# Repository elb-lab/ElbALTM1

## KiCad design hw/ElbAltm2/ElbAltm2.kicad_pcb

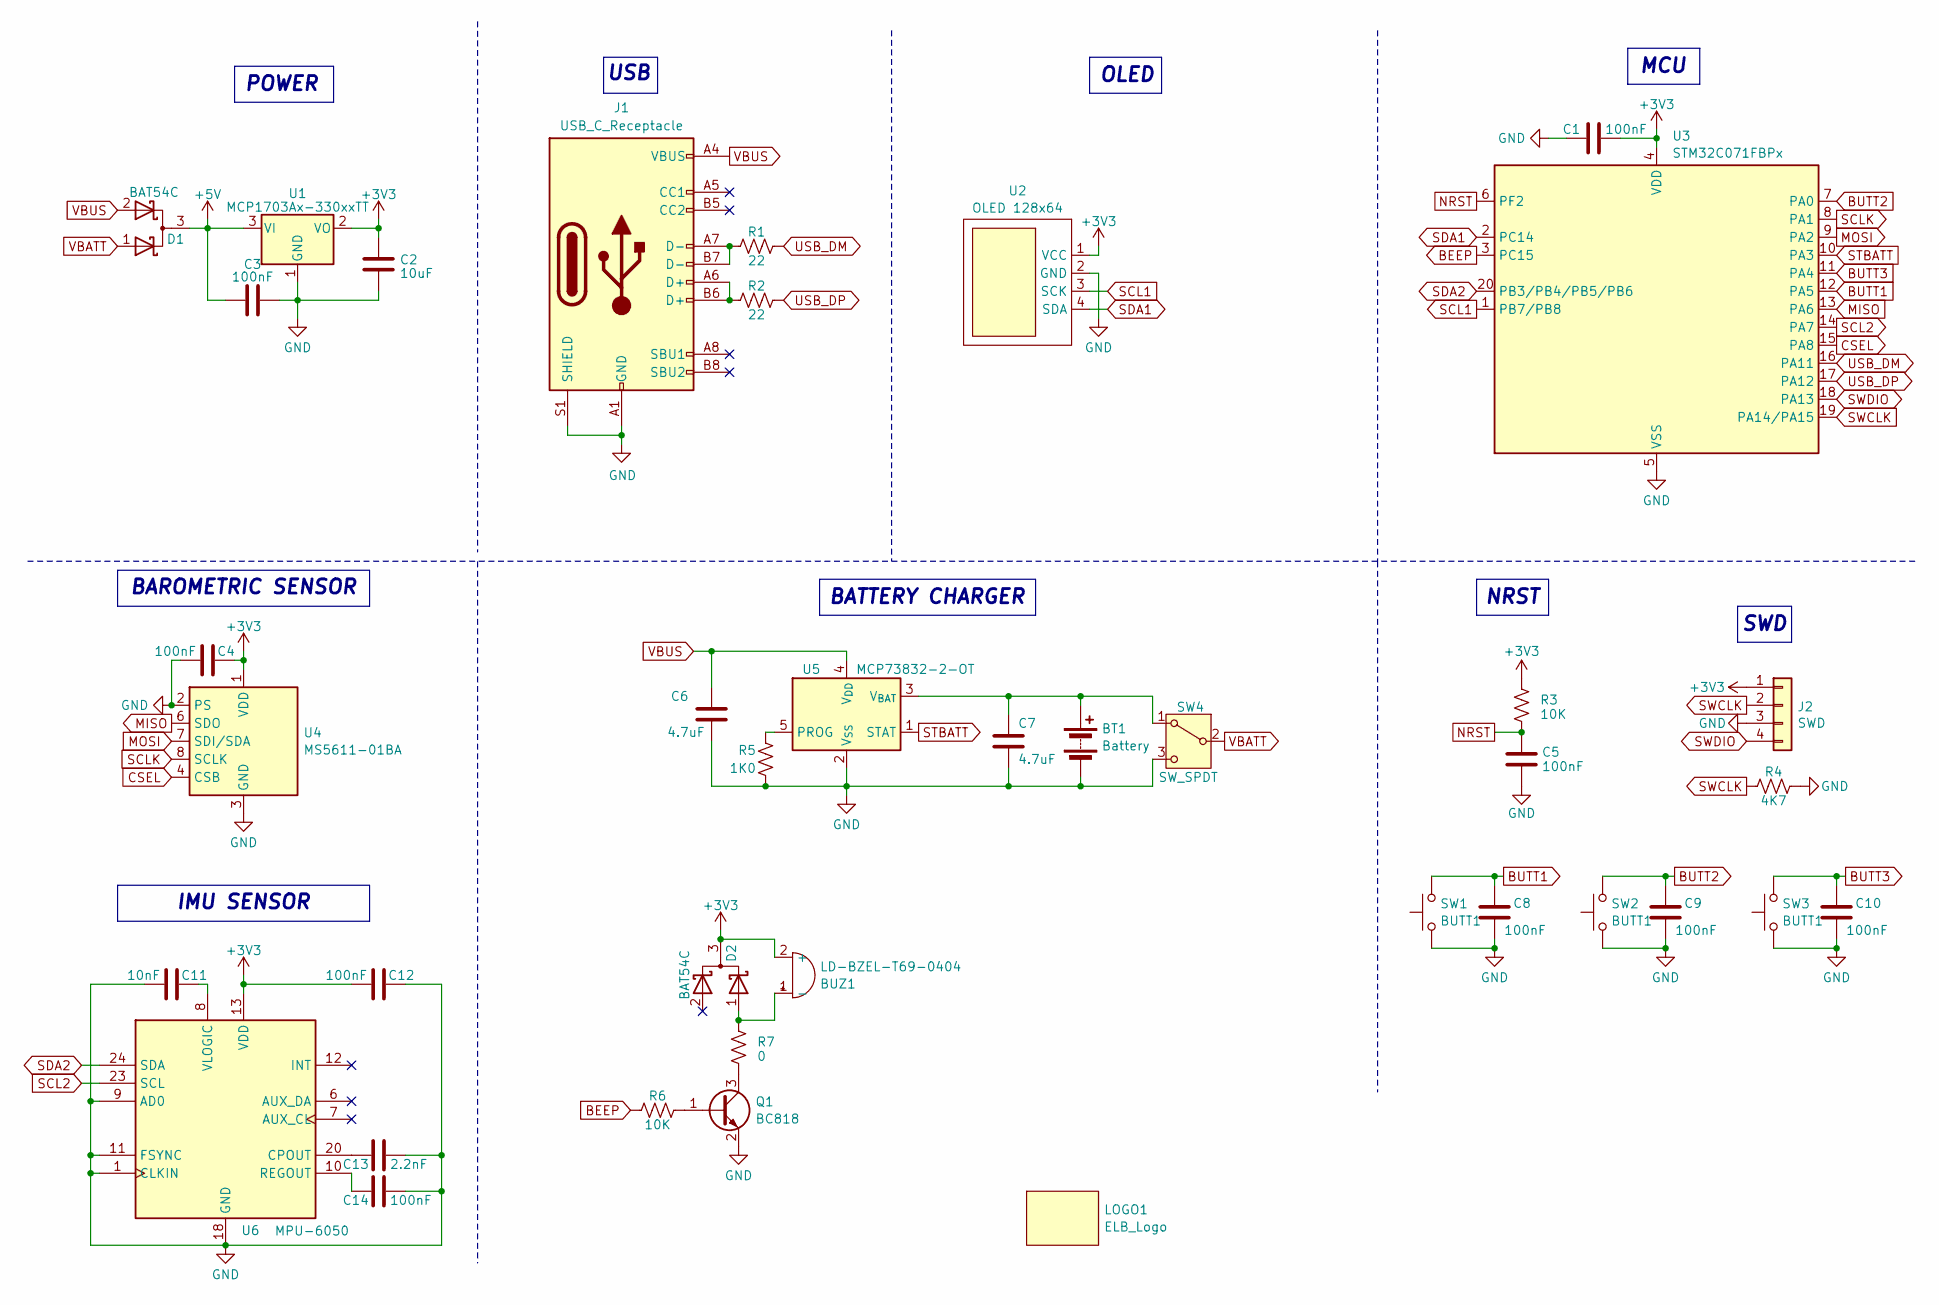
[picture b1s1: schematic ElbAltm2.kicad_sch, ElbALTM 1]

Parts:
BT1: Battery; JST_PH_S2B-PH-K_1x02_P2.00mm_Horizontal
BUZ1: LD-BZEL-T69-0404
C1, C3, C4, C5, C8, C9, C10, C12, C14: 100nF; C_0805_2012Metric_Pad1.18x1.45mm_HandSolder
C2: 10uF; C_0805_2012Metric_Pad1.18x1.45mm_HandSolder
C6, C7: 4.7uF; C_0805_2012Metric_Pad1.18x1.45mm_HandSolder
C11: 10nF; C_0805_2012Metric_Pad1.18x1.45mm_HandSolder
C13: 2.2nF; C_0805_2012Metric_Pad1.18x1.45mm_HandSolder
D1, D2: BAT54C; SOT-23
J1: USB_C_Receptacle; USB_C_Receptacle_HRO_TYPE-C-31-M-12
J2: SWD; PinHeader_1x04_P2.54mm_Horizontal
LOGO1: ELB_Logo; HDO_very_small_bn
Q1: BC818; SOT-23
R1, R2: 22; R_0805_2012Metric_Pad1.20x1.40mm_HandSolder
R3, R6: 10K; R_0805_2012Metric_Pad1.20x1.40mm_HandSolder
R4: 4K7; R_0805_2012Metric_Pad1.20x1.40mm_HandSolder
R5: 1K0; R_0805_2012Metric_Pad1.20x1.40mm_HandSolder
R7: 0; R_0805_2012Metric_Pad1.20x1.40mm_HandSolder
SW1, SW2, SW3: BUTT1; SW_Push_1P1T_NO_E-Switch_TL3301NxxxxxG
SW4: SW_SPDT; SW_SPDT_CK_JS102011SAQN
U1: MCP1703Ax-330xxTT; SOT-23
U2: OLED 128x64; oled128x64_wo_holes
U3: STM32C071FBPx; TSSOP-20_4.4x6.5mm_P0.65mm
U4: MS5611-01BA; LGA-8_3x5mm_P1.25mm
U5: MCP73832-2-OT; SOT-23-5
U6: MPU-6050; InvenSense_QFN-24_4x4mm_P0.5mm

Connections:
+3V3: BUZ1.2 (+), C1.1, C2.1, C4.1, C12.2, D2.3 (K), J2.1, R3.1, U1.2 (VO), U2.1 (VCC), U3.4 (VDD), U4.1 (VDD), U6.13 (VDD)
+5V: C3.1, D1.3 (K), U1.3 (VI)
BEEP: R6.1, U3.3 (PC15)
BUTT1: C8.1, SW1.2, U3.12 (PA5)
BUTT2: C9.1, SW2.2, U3.7 (PA0)
BUTT3: C10.1, SW3.2, U3.11 (PA4)
CSEL: U3.15 (PA8), U4.4 (CSB), U4.5 (CSB)
GND: BT1.2 (-), C1.2, C2.2, C3.2, C4.2, C5.2, C6.2, C7.2, C8.2, C9.2, C10.2, C11.2, C12.1, C13.2, C14.2, J1.A1 (GND), J1.A12 (GND), J1.B1 (GND), J1.B12 (GND), J1.S1 (SHIELD), J2.3, Q1.2 (E), R4.2, R5.2, SW1.1, SW2.1, SW3.1, SW4.3 (C), U1.1 (GND), U2.2 (GND), U3.5 (VSS), U4.2 (PS), U4.3 (GND), U5.2 (V_{SS}), U6.1 (CLKIN), U6.9 (AD0), U6.11 (FSYNC), U6.18 (GND)
MISO: U3.13 (PA6), U4.6 (SDO)
MOSI: U3.9 (PA2), U4.7 (SDI/SDA)
NRST: C5.1, R3.2, U3.6 (PF2)
unnamed: BT1.1 (+), C7.1, SW4.1 (A), U5.3 (V_{BAT})
unnamed: BUZ1.1 (-), D2.1 (A), R7.1
unnamed: J1.A6 (D+), J1.B6 (D+), R2.1
unnamed: J1.A7 (D-), J1.B7 (D-), R1.1
unnamed: Q1.1 (B), R6.2
unnamed: Q1.3 (C), R7.2
unnamed: R5.1, U5.5 (PROG)
unnamed: C13.1, U6.20 (CPOUT)
unnamed: C14.1, U6.10 (REGOUT)
unnamed: C11.1, U6.8 (VLOGIC)
SCL1: U2.3 (SCK), U3.1 (PB7/PB8)
SCL2: U3.14 (PA7), U6.23 (SCL)
SCLK: U3.8 (PA1), U4.8 (SCLK)
SDA1: U2.4 (SDA), U3.2 (PC14)
SDA2: U3.20 (PB3/PB4/PB5/PB6), U6.24 (SDA)
STBATT: U3.10 (PA3), U5.1 (STAT)
SWCLK: J2.2, R4.1, U3.19 (PA14/PA15)
SWDIO: J2.4, U3.18 (PA13)
USB_DM: R1.2, U3.16 (PA11)
USB_DP: R2.2, U3.17 (PA12)
VBATT: D1.1 (A), SW4.2 (B)
VBUS: C6.1, D1.2 (A), J1.A4 (VBUS), J1.A9 (VBUS), J1.B4 (VBUS), J1.B9 (VBUS), U5.4 (V_{DD})

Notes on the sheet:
SWD
IMU SENSOR
POWER
NRST
USB
BATTERY CHARGER
BAROMETRIC SENSOR
OLED
MCU

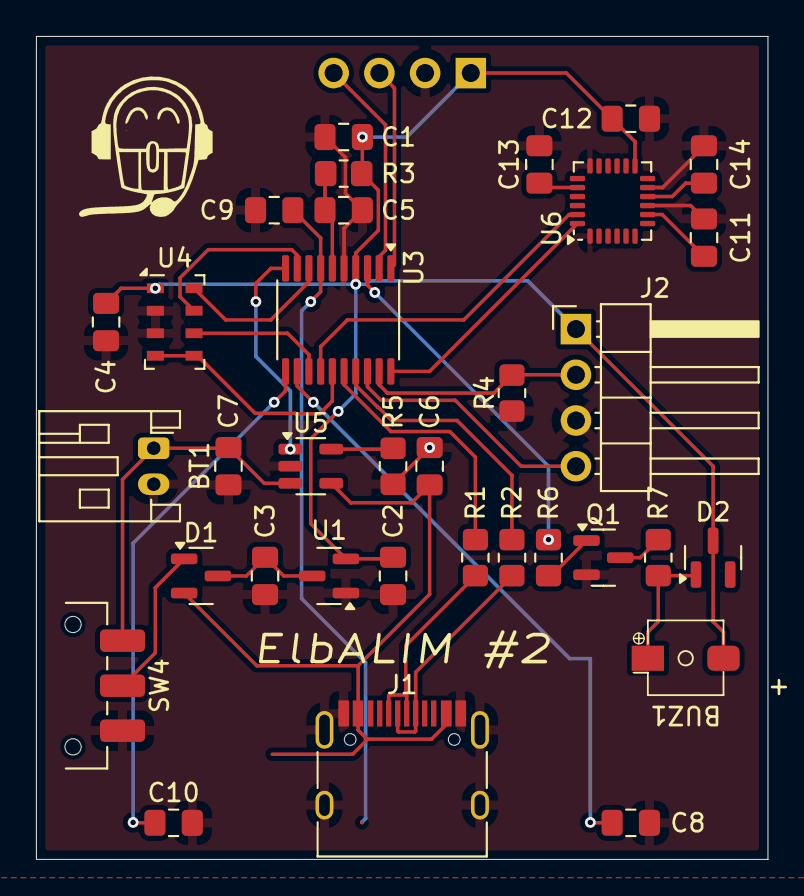
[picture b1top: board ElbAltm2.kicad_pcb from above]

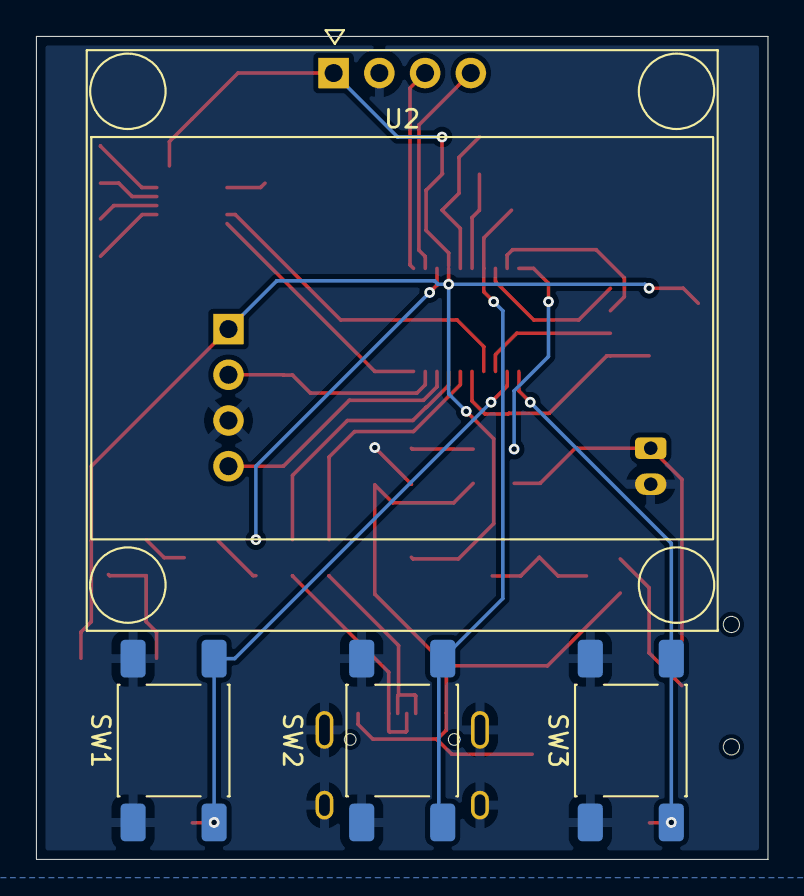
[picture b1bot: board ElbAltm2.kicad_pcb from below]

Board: 2 copper layers, 40.6 x 45.7 mm, 39 parts (4 on the bottom side), 33 nets.

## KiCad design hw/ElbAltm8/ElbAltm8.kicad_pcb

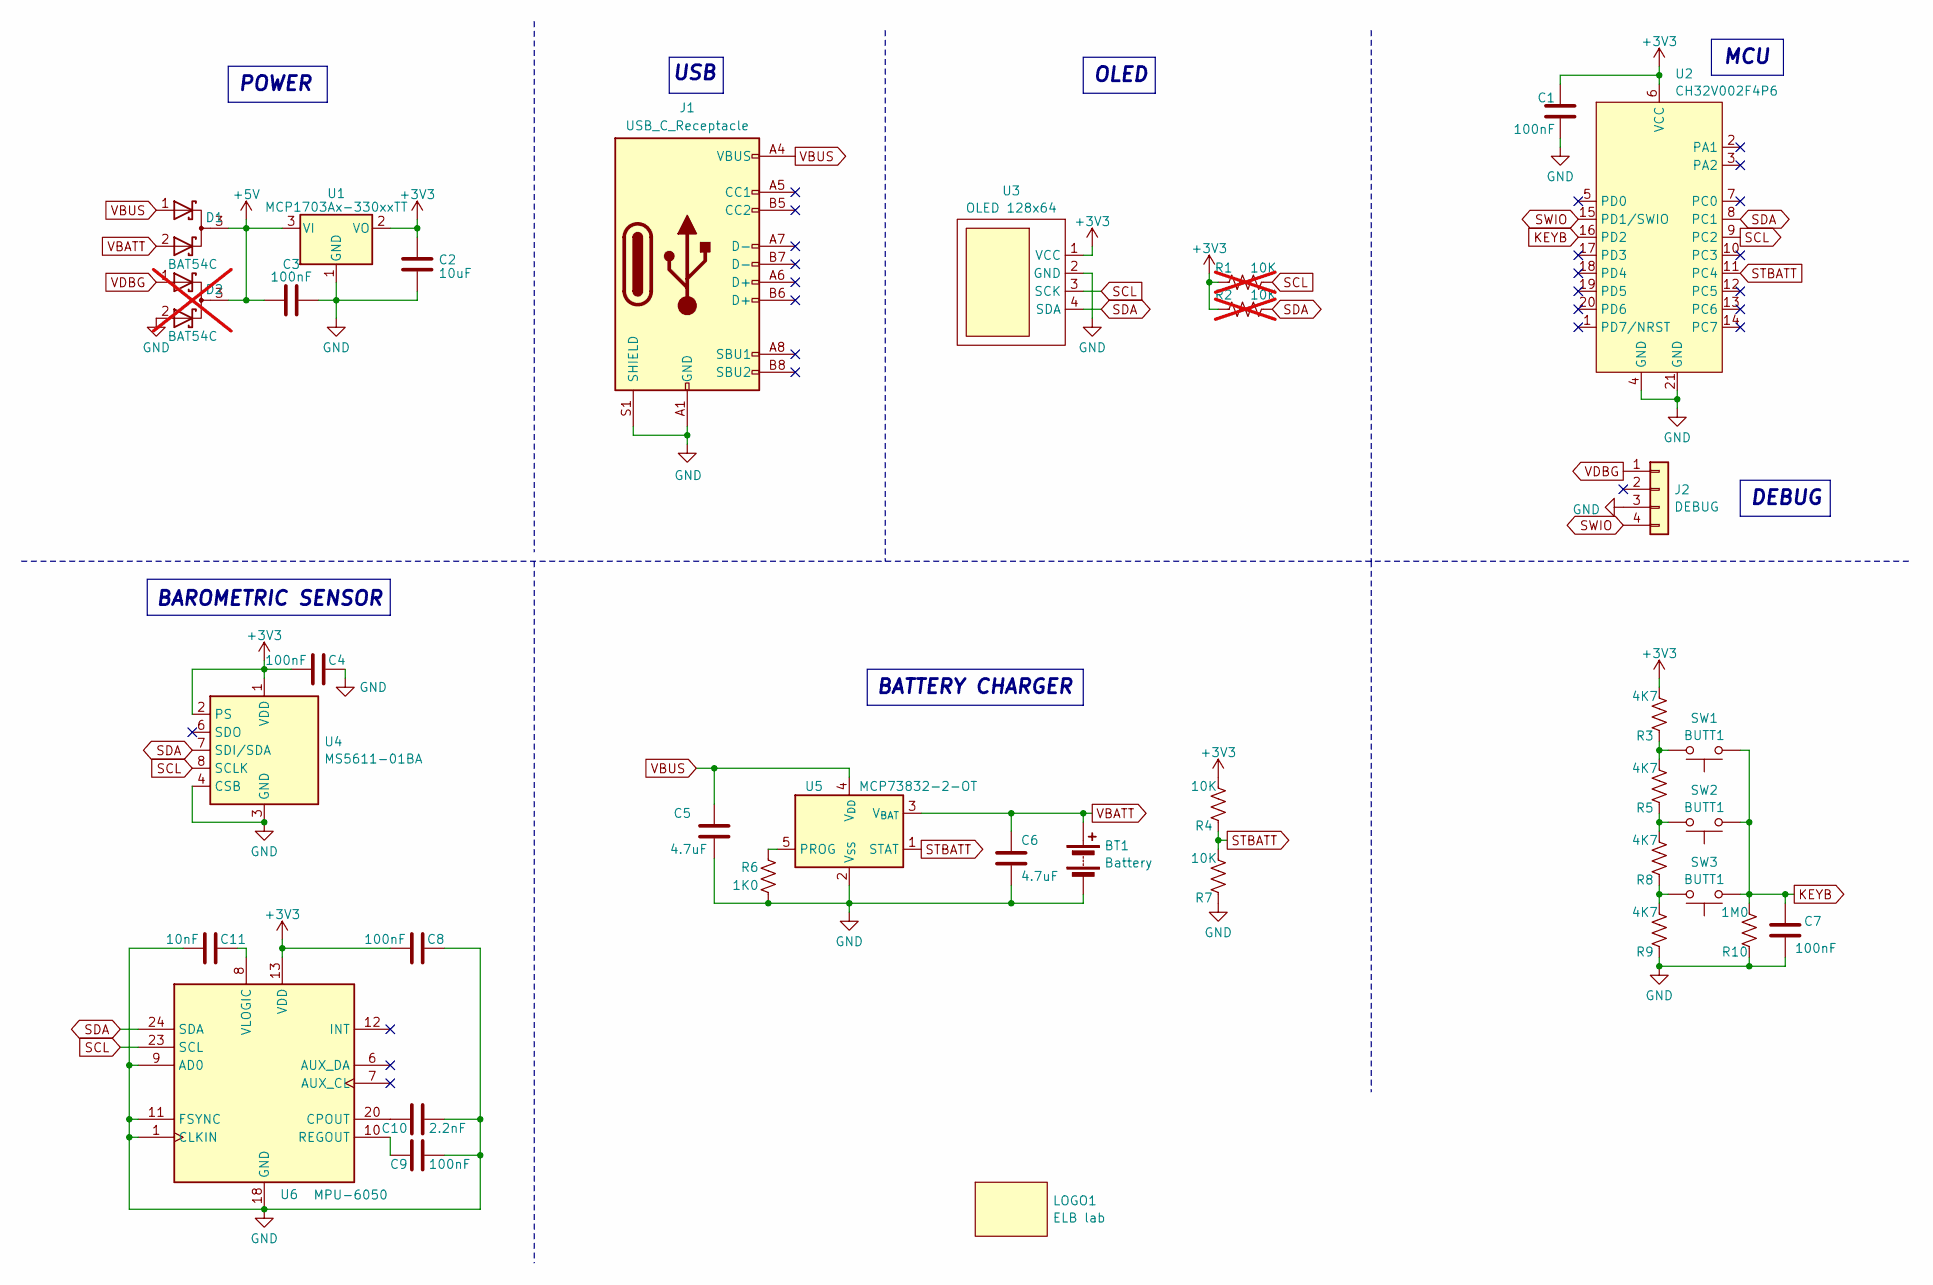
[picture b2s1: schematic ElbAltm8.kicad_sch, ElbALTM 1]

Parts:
BT1: Battery; JST_PH_B2B-PH-K_1x02_P2.00mm_Vertical
C1, C3, C4, C7, C8, C9: 100nF; C_0805_2012Metric_Pad1.18x1.45mm_HandSolder
C2: 10uF; C_0805_2012Metric_Pad1.18x1.45mm_HandSolder
C5, C6: 4.7uF; C_0805_2012Metric_Pad1.18x1.45mm_HandSolder
C10: 2.2nF; C_0805_2012Metric_Pad1.18x1.45mm_HandSolder
C11: 10nF; C_0805_2012Metric_Pad1.18x1.45mm_HandSolder
D1: BAT54C; SOT-23
D2: BAT54C; SOT-23; not fitted
J1: USB_C_Receptacle; USB_C_Receptacle_HRO_TYPE-C-31-M-12
J2: DEBUG; PinHeader_1x04_P2.54mm_Horizontal
LOGO1: ELB lab; HDO_very_small_bn
R1, R2: 10K; R_0805_2012Metric_Pad1.20x1.40mm_HandSolder; not fitted
R3, R5, R8, R9: 4K7; R_0805_2012Metric_Pad1.20x1.40mm_HandSolder
R4, R7: 10K; R_0805_2012Metric_Pad1.20x1.40mm_HandSolder
R6: 1K0; R_0805_2012Metric_Pad1.20x1.40mm_HandSolder
R10: 1M0; R_0805_2012Metric_Pad1.20x1.40mm_HandSolder
SW1, SW2, SW3: BUTT1; SW_PUSH_6mm_H5mm
U1: MCP1703Ax-330xxTT; SOT-23
U2: CH32V002F4P6; QFN-20-1EP_3x3mm_P0.4mm_EP1.65x1.65mm_ThermalVias
U3: OLED 128x64; oled128x64_wo_holes
U4: MS5611-01BA; LGA-8_3x5mm_P1.25mm
U5: MCP73832-2-OT; SOT-23-5
U6: MPU-6050; InvenSense_QFN-24_4x4mm_P0.5mm

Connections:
+3V3: C1.1, C2.1, C4.2, C8.2, R1.1, R2.1, R3.2, R4.2, U1.2 (VO), U2.6 (VCC), U3.1 (VCC), U4.1 (VDD), U4.2 (PS), U6.13 (VDD)
+5V: C3.1, D1.3 (K), D2.3 (K), U1.3 (VI)
GND: BT1.2 (-), C1.2, C2.2, C3.2, C4.1, C5.2, C6.2, C7.2, C8.1, C9.2, C10.2, C11.2, D2.2 (A), J1.A1 (GND), J1.A12 (GND), J1.B1 (GND), J1.B12 (GND), J1.S1 (SHIELD), J2.3, R6.2, R7.1, R9.1, R10.1, U1.1 (GND), U2.4 (GND), U2.21 (GND), U3.2 (GND), U4.3 (GND), U4.4 (CSB), U4.5 (CSB), U5.2 (V_{SS}), U6.1 (CLKIN), U6.9 (AD0), U6.11 (FSYNC), U6.18 (GND)
KEYB: C7.1, R10.2, SW1.1, SW2.1, SW3.1, U2.16 (PD2)
unnamed: R3.1, R5.2, SW1.2
unnamed: R5.1, R8.2, SW2.2
unnamed: R8.1, R9.2, SW3.2
unnamed: R6.1, U5.5 (PROG)
unnamed: C10.1, U6.20 (CPOUT)
unnamed: C9.1, U6.10 (REGOUT)
unnamed: C11.1, U6.8 (VLOGIC)
SCL: R1.2, U2.9 (PC2), U3.3 (SCK), U4.8 (SCLK), U6.23 (SCL)
SDA: R2.2, U2.8 (PC1), U3.4 (SDA), U4.7 (SDI/SDA), U6.24 (SDA)
STBATT: R4.1, R7.2, U2.11 (PC4), U5.1 (STAT)
SWIO: J2.4, U2.15 (PD1/SWIO)
VBATT: BT1.1 (+), C6.1, D1.2 (A), U5.3 (V_{BAT})
VBUS: C5.1, D1.1 (A), J1.A4 (VBUS), J1.A9 (VBUS), J1.B4 (VBUS), J1.B9 (VBUS), U5.4 (V_{DD})
VDBG: D2.1 (A), J2.1

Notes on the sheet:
POWER
USB
BATTERY CHARGER
DEBUG
BAROMETRIC SENSOR
OLED
MCU

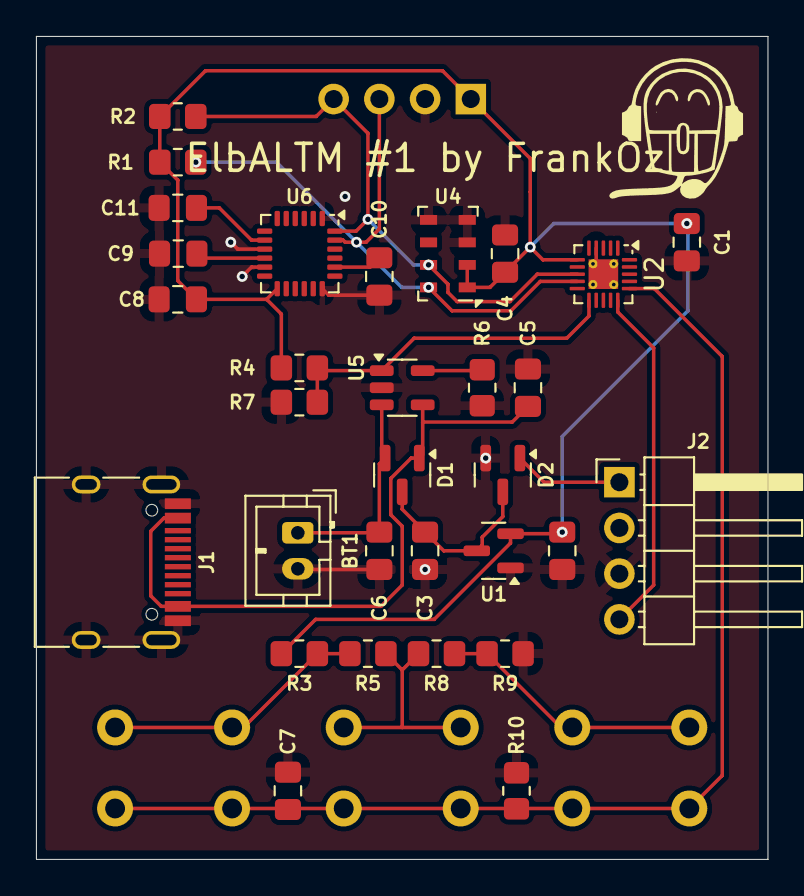
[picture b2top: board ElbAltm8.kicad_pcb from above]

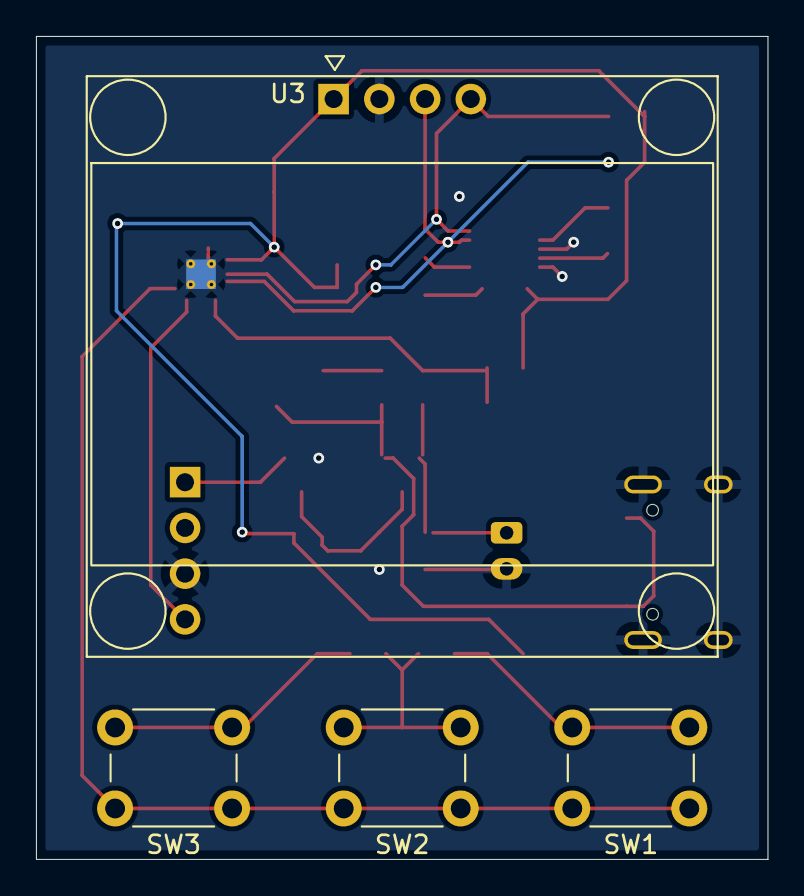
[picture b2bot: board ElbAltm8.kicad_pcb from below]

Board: 2 copper layers, 40.6 x 45.7 mm, 36 parts (4 on the bottom side), 18 nets.

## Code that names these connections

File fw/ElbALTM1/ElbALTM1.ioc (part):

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Mcu.Name=STM32C071FBPx
Mcu.Package=TSSOP20_GP
Mcu.UserName=STM32C071FBPx
PA0.GPIOParameters=GPIO_PuPd,GPIO_Label,GPIO_ModeDefaultEXTI
PA0.GPIO_Label=BUTT2
PA0.GPIO_ModeDefaultEXTI=GPIO_MODE_IT_FALLING
PA0.GPIO_PuPd=GPIO_PULLUP
PA0.Signal=GPXTI0
PA1.GPIOParameters=GPIO_Speed,GPIO_Label
PA1.GPIO_Label=SCLK
PA1.GPIO_Speed=GPIO_SPEED_FREQ_VERY_HIGH
PA1.Mode=Full_Duplex_Master
PA1.Signal=SPI1_SCK
PA11\ [PA9].Signal=USB_DM
PA12\ [PA10].Signal=USB_DP
PA13.GPIOParameters=GPIO_Label
PA13.GPIO_Label=SWDIO
PA13.Mode=Serial_Wire
PA13.Signal=DEBUG_SWDIO
PA14-BOOT0.GPIOParameters=GPIO_Label
PA14-BOOT0.GPIO_Label=SWCLK
PA14-BOOT0.Mode=Serial_Wire
PA14-BOOT0.Signal=DEBUG_SWCLK
PA14-BOOT0__PA15.StandardMode=true
PA2.GPIOParameters=GPIO_Speed,GPIO_Label
PA2.GPIO_Label=MOSI
PA2.GPIO_Speed=GPIO_SPEED_FREQ_VERY_HIGH
PA2.Mode=Full_Duplex_Master
PA2.Signal=SPI1_MOSI
PA3.GPIOParameters=GPIO_PuPd,GPIO_Label
PA3.GPIO_Label=STBATT
PA3.GPIO_PuPd=GPIO_PULLUP
PA3.Signal=GPIO_Input
PA4.GPIOParameters=GPIO_PuPd,GPIO_Label,GPIO_Mode
PA4.GPIO_Label=BUTT3
PA4.GPIO_Mode=GPIO_MODE_INPUT
PA4.GPIO_PuPd=GPIO_PULLUP
PA4.Signal=GPIO_Input
PA5.GPIOParameters=GPIO_PuPd,GPIO_Label,GPIO_Mode
PA5.GPIO_Label=BUTT1
PA5.GPIO_Mode=GPIO_MODE_INPUT
PA5.GPIO_PuPd=GPIO_PULLUP
PA5.Signal=GPIO_Input
PA6.GPIOParameters=GPIO_Speed,GPIO_Label
PA6.GPIO_Label=MISO
PA6.GPIO_Speed=GPIO_SPEED_FREQ_VERY_HIGH
PA6.Mode=Full_Duplex_Master
PA6.Signal=SPI1_MISO
PA7.GPIOParameters=GPIO_Speed,GPIO_Label,GPIO_Pu
PA7.GPIO_Label=SCL2
PA7.GPIO_Pu=GPIO_PULLUP
PA7.GPIO_Speed=GPIO_SPEED_FREQ_VERY_HIGH
PA7.Mode=I2C
PA7.Signal=I2C2_SCL
PA8.GPIOParameters=GPIO_Speed,PinState,GPIO_Label
PA8.GPIO_Label=CSEL
PA8.GPIO_Speed=GPIO_SPEED_FREQ_VERY_HIGH
PA8.PinState=GPIO_PIN_SET
PA8.Signal=GPIO_Output
PB3__PB4__PB5__PB6.StandardMode=true
PB4.GPIOParameters=GPIO_Speed,GPIO_Label,GPIO_Pu
PB4.GPIO_Label=SDA2
PB4.GPIO_Pu=GPIO_PULLUP
PB4.GPIO_Speed=GPIO_SPEED_FREQ_VERY_HIGH
PB4.Mode=I2C
PB4.Signal=I2C2_SDA
PB7.GPIOParameters=GPIO_Speed,GPIO_Label,GPIO_Pu,GPIO_FM7
PB7.GPIO_FM7=SYSCFG_FASTMODEPLUS_PB7
PB7.GPIO_Label=SCL1
PB7.GPIO_Pu=GPIO_PULLUP
PB7.GPIO_Speed=GPIO_SPEED_FREQ_VERY_HIGH
PB7.Mode=I2C
PB7.Signal=I2C1_SCL
PB7__PB8.StandardMode=true
PC14-OSCX_IN(PC14).GPIOParameters=GPIO_Speed,GPIO_Label,GPIO_FMPC14,GPIO_Pu
PC14-OSCX_IN(PC14).GPIO_FMPC14=SYSCFG_FASTMODEPLUS_PC14
PC14-OSCX_IN(PC14).GPIO_Label=SDA1
PC14-OSCX_IN(PC14).GPIO_Pu=GPIO_PULLUP
PC14-OSCX_IN(PC14).GPIO_Speed=GPIO_SPEED_FREQ_VERY_HIGH
PC14-OSCX_IN(PC14).Mode=I2C
PC14-OSCX_IN(PC14).Signal=I2C1_SDA
PC15-OSCX_OUT(PC15).GPIOParameters=GPIO_Speed,GPIO_PuPd,GPIO_Label
PC15-OSCX_OUT(PC15).GPIO_Label=BEEP
PC15-OSCX_OUT(PC15).GPIO_PuPd=GPIO_PULLDOWN
PC15-OSCX_OUT(PC15).GPIO_Speed=GPIO_SPEED_FREQ_VERY_HIGH
PC15-OSCX_OUT(PC15).Signal=S_TIM3_CH3
RCC.HSE_VALUE=8000000
RCC.SYSCLKFreq_VALUE=48000000
RCC.SYSCLKSource=RCC_SYSCLKSOURCE_HSIUSB48
board=custom

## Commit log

2025-07-31 Primo commit
2025-07-31 Aggiunta font 48px
2025-08-03 Ritardo prima della inizializzazione OLED
2025-08-04 Correzione calcolo altimetrico
2025-08-06 Menu tabellare
2025-08-07 Skroll videata
2025-08-08 Skroll di tutti i dati + fermata centrale
2025-08-09 Skroll menu dx/rx + correzione formula x calcolo quota
2025-08-09 Aggiunta titolo + modulo IMG
2025-08-09 Backup
2025-08-11 Spegnimento
2025-08-12 Skrool continuo
2025-08-12 Blocco Skrool + Release firmware
2025-09-02 Aggiornamento toolchain da 1.18.2 a 1.19.0
